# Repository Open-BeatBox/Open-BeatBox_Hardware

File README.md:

# Open-BEATBox — Hardware

CAD sources, electronics designs and production files for the Open-BEATBox
apparatus.

## Contents

- `mechanical/` — 3D models and production files (3D printing, laser cutting) for the enclosure and modules, two hardware generations, **V2** and **V3**.
- `electronics/` — KiCad circuit-board designs and manufacturing files for the V3 modules.

## `mechanical/`

### `mechanical/V2/`

SolidWorks sources (`.SLDPRT` parts, `.SLDASM` assemblies), reference renders
(`.png`) and one drawing (`cage_1feeder_2screens.pdf`), organised per module:

| Folder | Module |
| --- | --- |
| `baseCage/` | base cage |
| `cage_1feeder_2screens/` | cage assembly with one feeder and two screens |
| `camera/` | camera and NeoPixel ring support |
| `feeder/` | feeder part and assembly |
| `passage/` | passage |
| `screen/` | screen frame |

Each module has a `production/` subfolder with the files sent to manufacturing:
`.STL` meshes for 3D printing, `.DXF` outlines for laser cutting (the filenames
carry the intended material and thickness, e.g. `..._3mm_clear.DXF`), and
sliced `.gcode` whose filenames indicate a Creality K1 Max, 0.4 mm nozzle and
Hyper PLA.

### `mechanical/V3/`

Neutral-format sources per module — `feeder/`, `lighting/`, `main/` (Raspberry
Pi shield), `screen/`, `tunnel/` — each with a `.STEP` file, a `.zip` archive
of the native CAD project, and a `PRODUCTION/` subfolder of `.STL` files (plus
one `.DXF` under `lighting/`). Alongside the modules:

| Folder | Contents |
| --- | --- |
| `enclosure/` | 3 mm wall, door and ceiling panels and the 10 mm base plate as `.DXF` for laser cutting, plus the door knob `.STL` |
| `structure/` | base plate `.DXF` and pillar `.STL` |
| `final_assembly/` | `.zip` archive of the complete assembly |

## `electronics/`

One KiCad project per PCB (`BB_RPI_shield_V1`, `BB_feeder_main_V1`,
`BB_feeder_IRBarrier_V1`, `BB_lighting_V1`, `BB_screen_main_V1`,
`BB_IR_light_curtain_V2_38k`, `BB_tunnel_V1`, `BB_nosepoke_V1`), each with its
schematic exported to PDF and a `production/` folder holding the Gerber `.zip`,
BOM, pick-and-place files and IPC netlist. `STEPs/` has 3D models of the
boards and `pictures/` has renders. See
[`electronics/README.md`](./electronics/README.md) for what each board does.

Component datasheets are not included: they are the manufacturers' documents,
available from their websites (the BOM in each `production/` folder names the
parts).

## Large files

`.zip` and `.STEP` files are stored with [Git LFS](https://git-lfs.com/).
Install it before cloning (`git lfs install`), or those files will arrive as
small pointer files. Release archives and the Zenodo record contain the full
files.

## History

`mechanical/V3/` and `electronics/` were imported with their full commit history
from the ICM GitLab project `icm-institute/rnd/projects/burguiere_beatbox_website`
(`02_CAD_files/V3` and `03_ECAD_files` on its `main` branch). They were later
renamed from `CAD_files/` and `ECAD_files/`; use `git log --follow <file>` to
see a file's history across the renames.

## Licence

CERN Open Hardware Licence Version 2 — Strongly Reciprocal
(**CERN-OHL-S-2.0**). See [`LICENSE`](./LICENSE).

## Citing

If you use these designs in published work, please cite **both**:

1. the reference preprint of the platform:

   > Euvrard M, Benzina N, Domingues D, Mondragón-González SL, Huzard D, Penderia G, Travert-Jouanneau Y, Lavielle O, Lousada E, Schreiweis C, Lorenz A, Pavlov P, Ajili Z, Lebegue L, Tissier P, Burguière E. "Open-BEATBox: an open-source autonomous operant chamber for high-throughput data acquisition of complex behaviour." bioRxiv, 2026. doi: [10.64898/2026.11.07.765109](https://doi.org/10.64898/2026.11.07.765109)

2. the Zenodo record of the release you used. Each release of this repository
   is archived on Zenodo with its own DOI; the version described in the
   preprint is release `biorxiv-v1` (DOI [10.5281/zenodo.24080048](https://doi.org/10.5281/zenodo.24080048);
   all versions: [10.5281/zenodo.24080047](https://doi.org/10.5281/zenodo.24080047)). `CITATION.cff` carries the metadata (GitHub's
   *Cite this repository* button).

## Related repositories

- [Open-BeatBox_Software](https://github.com/Open-BeatBox/Open-BeatBox_Software) — PC application and module firmware (AGPL-3.0-or-later)
- [Open-BeatBox_Documentation](https://github.com/Open-BeatBox/Open-BeatBox_Documentation) — manual, assembly tutorials, Master BOM (CC-BY-4.0)
- [Open-BeatBox.github.io](https://github.com/Open-BeatBox/Open-BeatBox.github.io) — project website and manual build pipeline
- [Open-BeatBox_Firmware](https://github.com/Open-BeatBox/Open-BeatBox_Firmware) — placeholder pointing to the firmware in the Software repository

## Project links

- Project website: https://open-beatbox.github.io/
- Manual: https://open-beatbox.github.io/docs/manual/

## Issues

Please report problems with these CAD and electronics files in this repository's
[issue tracker](https://github.com/Open-BeatBox/Open-BeatBox_Hardware/issues).

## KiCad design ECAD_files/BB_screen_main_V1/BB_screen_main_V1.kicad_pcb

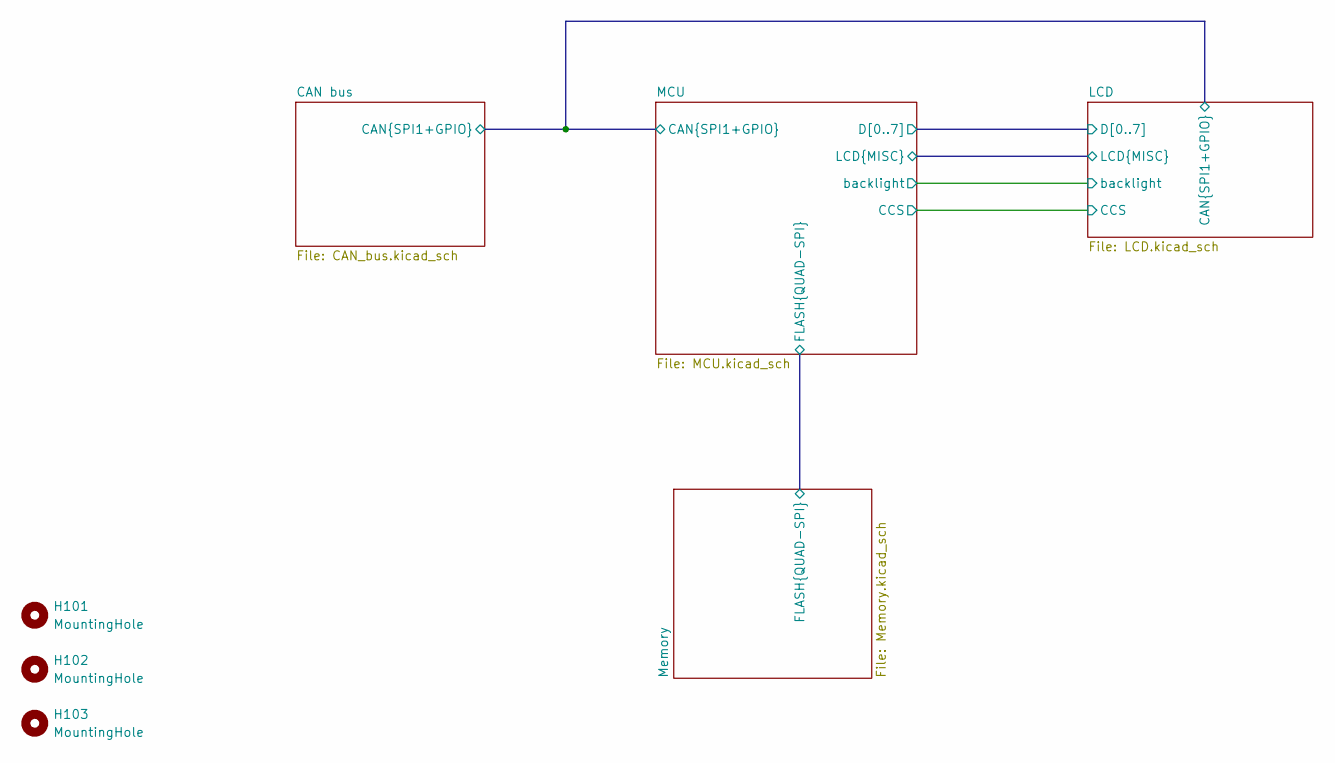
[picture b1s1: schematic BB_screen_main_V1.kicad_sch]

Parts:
H101, H102, H103: MountingHole; MountingHole_3.2mm_M3_Pad_TopBottom

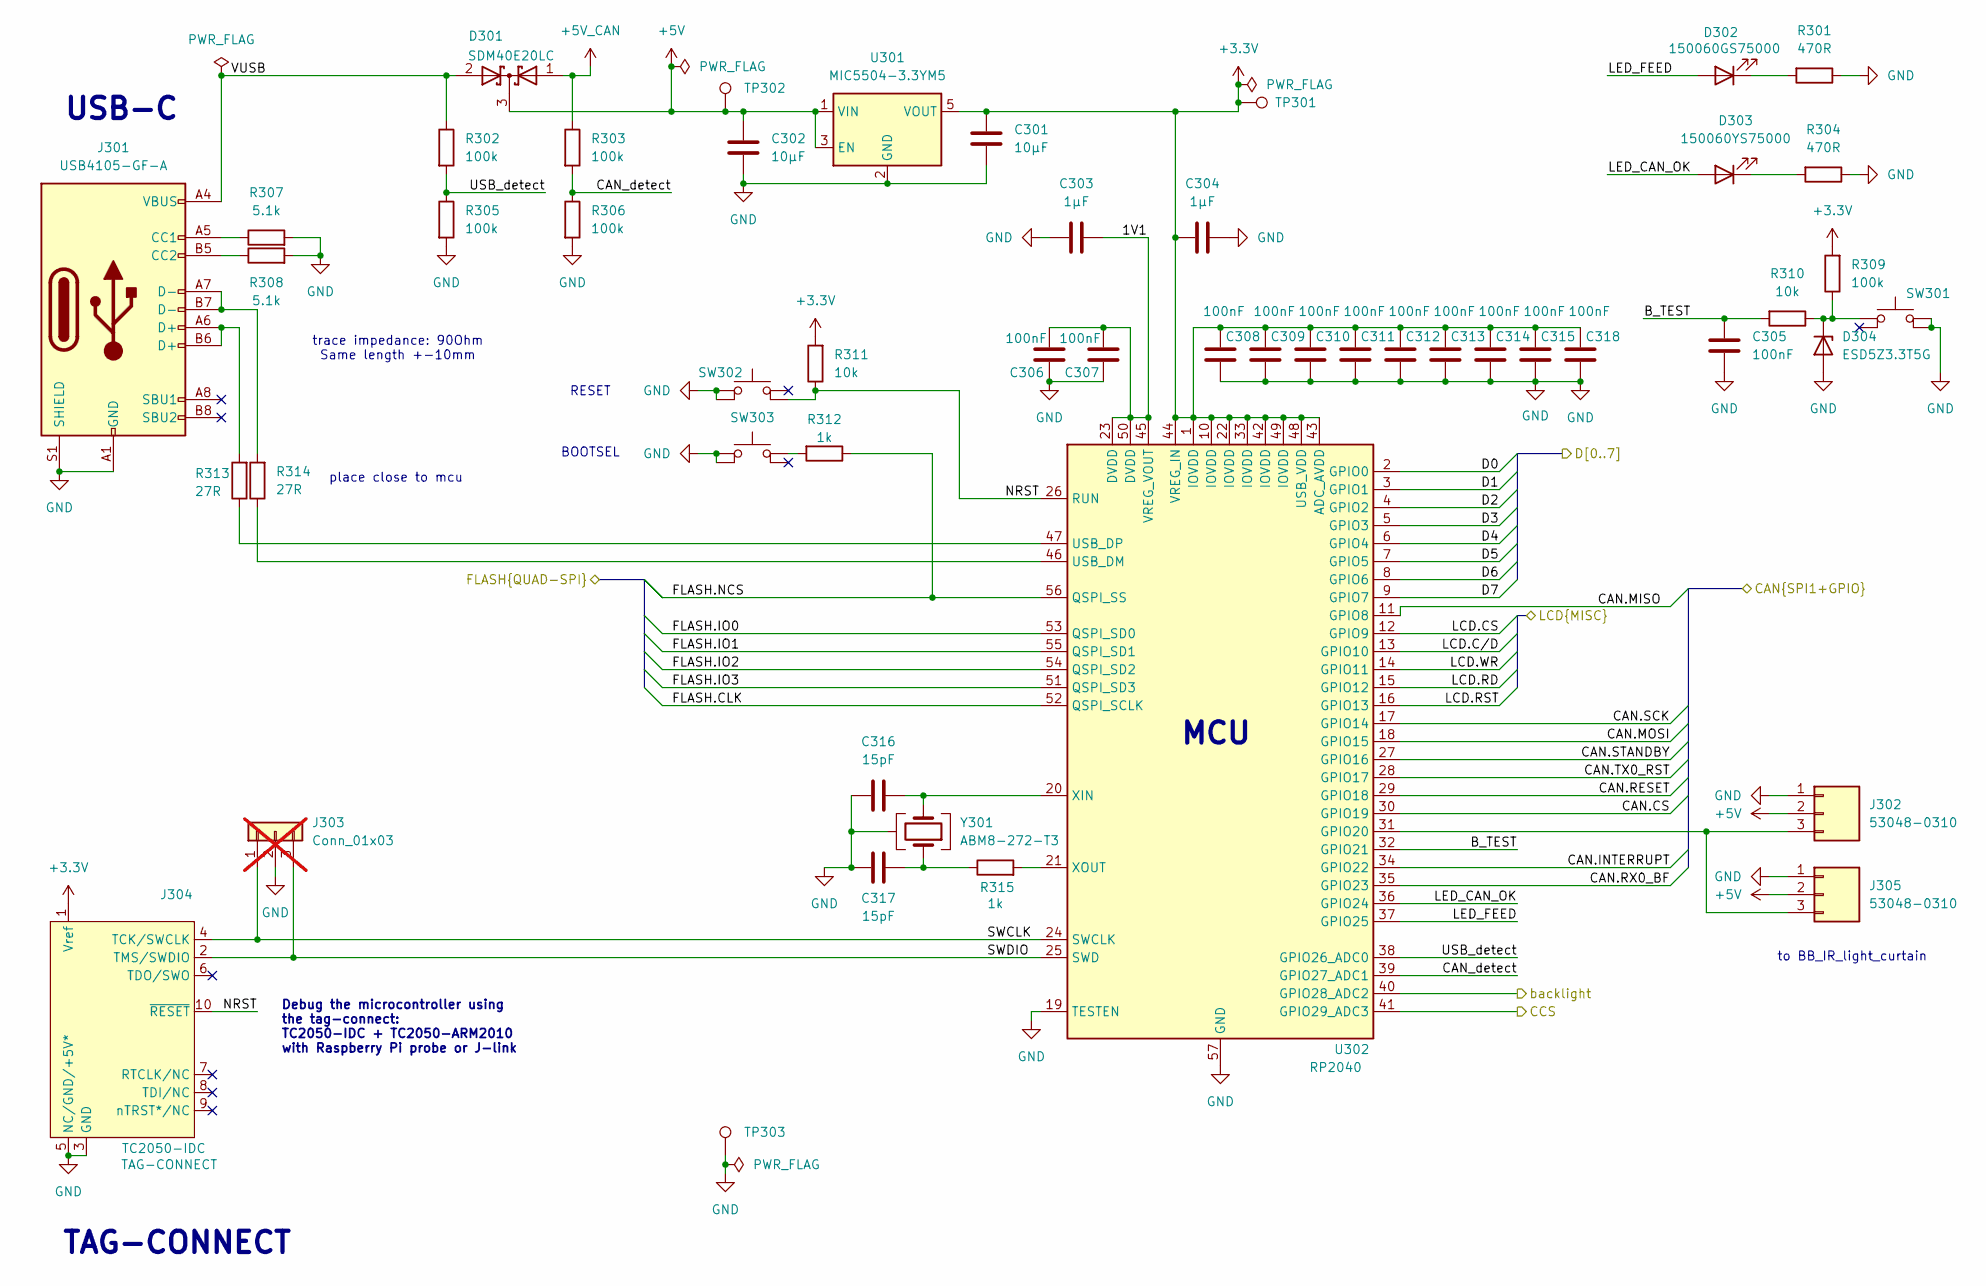
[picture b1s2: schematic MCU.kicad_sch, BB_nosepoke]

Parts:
C301, C302: 10µF; C_0603_1608Metric
C303, C304: 1µF; C_0603_1608Metric
C305, C306, C307, C308, C309, C310, C311, C312, C313, C314, C315, C318: 100nF; C_0603_1608Metric
C316, C317: 15pF; C_0603_1608Metric
D301: D_SDM40E20LC; SOT-23; MPN SDM40E20LC; JLC Part C155330
D302: LED_150060GS75000; LED_0603_1608Metric; MPN 150060GS75000; JLC Part C5252984
D303: LED_150060YS75000; LED_0603_1608Metric; MPN 150060YS75000; JLC Part C6784997
D304: TVS_ESD5Z3.3T5G; D_SOD-523; MPN ESD5Z3.3T5G; JLC Part C22440024
J301: Conn_USB-C_USB4105-GF-A; Conn_USB_C_Receptacle_GCT_USB4105-xx-A_16P_TopMnt_Horizontal; MPN USB4105-GF-A; JLC Part C393939
J302, J305: Conn_Picoblade_Molex_53048-0310; Conn_Molex_PicoBlade_53048-0310_1x03_P1.25mm_Horizontal; MPN 53048-0310; JLC Part C505275
J303: Conn_01x03; PinHeader_1x03_P2.54mm_Vertical; not fitted
J304: Conn_TagConnect_TC2050-IDC; Tag-Connect_TC2050-IDC-FP_2x05_P1.27mm_Vertical; MPN TC2050-IDC
R301, R304: 470R; R_0603_1608Metric
R302, R303, R305, R306, R309: 100k; R_0603_1608Metric
R307, R308: 5.1k; R_0603_1608Metric
R310, R311: 10k; R_0603_1608Metric
R312, R315: 1k; R_0603_1608Metric
R313, R314: 27R; R_0603_1608Metric
SW301, SW302, SW303: SW_TL3305AF160QG; SW_Push_TL3305; MPN TL3305AF160QG; JLC Part C18078070
TP301, TP302, TP303: TestPoint; TestPoint_THTPad_D2.0mm_Drill1.0mm
U301: MIC5504-3.3YM5; SOT-23-5; MPN MIC5504-3.3YM5; JLC Part C88419
U302: RP2040; QFN-56-1EP_7x7mm_P0.4mm_EP3.2x3.2mm; MPN RP2040; JLC Part C2040
Y301: Crystal_ABM8-272-T3; Crystal_SMD_Abracon_ABM8; MPN ABM8-272-T3; JLC Part C20625731

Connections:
+3.3V: C301.1, C304.1, C308.1, C309.1, C310.1, C311.1, C312.1, C313.1, C314.1, C315.1, C318.1, J304.1 (Vref), R309.2, R311.2, TP301.1 (1_1), U301.5 (VOUT), U302.1 (IOVDD), U302.10 (IOVDD), U302.22 (IOVDD), U302.33 (IOVDD), U302.42 (IOVDD), U302.43 (ADC_AVDD), U302.44 (VREG_IN), U302.48 (USB_VDD), U302.49 (IOVDD); also elsewhere on the board
/CAN bus/CAN.CS: U302.30 (GPIO19); also elsewhere on the board
/CAN bus/CAN.INTERRUPT: U302.34 (GPIO22); also elsewhere on the board
/CAN bus/CAN.MISO: U302.11 (GPIO8); also elsewhere on the board
/CAN bus/CAN.MOSI: U302.18 (GPIO15); also elsewhere on the board
/CAN bus/CAN.RESET: U302.29 (GPIO18); also elsewhere on the board
/CAN bus/CAN.RX0_BF: U302.35 (GPIO23); also elsewhere on the board
/CAN bus/CAN.SCK: U302.17 (GPIO14); also elsewhere on the board
/CAN bus/CAN.STANDBY: U302.27 (GPIO16); also elsewhere on the board
/CAN bus/CAN.TX0_RST: U302.28 (GPIO17); also elsewhere on the board
/LCD/CCS: R302.2, R305.1, U302.38 (GPIO26_ADC0); also elsewhere on the board
/LCD/D0: U302.2 (GPIO0); also elsewhere on the board
/LCD/D1: U302.3 (GPIO1); also elsewhere on the board
/LCD/D2: U302.4 (GPIO2); also elsewhere on the board
/LCD/D3: U302.5 (GPIO3); also elsewhere on the board
/LCD/D4: U302.6 (GPIO4); also elsewhere on the board
/LCD/D5: U302.7 (GPIO5); also elsewhere on the board
/LCD/D6: U302.8 (GPIO6); also elsewhere on the board
/LCD/D7: U302.9 (GPIO7); also elsewhere on the board
/LCD/LCD.CS: U302.12 (GPIO9); also elsewhere on the board
/LCD/LCD.C/D: U302.13 (GPIO10); also elsewhere on the board
/LCD/LCD.RD: U302.15 (GPIO12); also elsewhere on the board
/LCD/LCD.RST: U302.16 (GPIO13); also elsewhere on the board
/LCD/LCD.WR: U302.14 (GPIO11); also elsewhere on the board
/LCD/backlight: U302.40 (GPIO28_ADC2); also elsewhere on the board
/MCU/1V1: C303.2, C306.2, C307.1, U302.23 (DVDD), U302.45 (VREG_VOUT), U302.50 (DVDD)
/MCU/B_TEST: C305.1, R310.2, U302.32 (GPIO21)
/MCU/CAN_detect: R303.2, R306.1, U302.39 (GPIO27_ADC1)
/MCU/FLASH.CLK: U302.52 (QSPI_SCLK); also elsewhere on the board
/MCU/FLASH.IO0: U302.53 (QSPI_SD0); also elsewhere on the board
/MCU/FLASH.IO1: U302.55 (QSPI_SD1); also elsewhere on the board
/MCU/FLASH.IO2: U302.54 (QSPI_SD2); also elsewhere on the board
/MCU/FLASH.IO3: U302.51 (QSPI_SD3); also elsewhere on the board
/MCU/FLASH.NCS: R312.1, U302.56 (QSPI_SS); also elsewhere on the board
/MCU/LED_CAN_OK: D303.2 (A), U302.36 (GPIO24)
/MCU/LED_FEED: D302.2 (A), U302.37 (GPIO25)
/MCU/NRST: J304.10 (~RESET), R311.1, SW302.2, U302.26 (RUN)
/MCU/SWCLK: J303.1, J304.4 (TCK/SWCLK), U302.24 (SWCLK)
/MCU/SWDIO: J303.3, J304.2 (TMS/SWDIO), U302.25 (SWD)
/MCU/VUSB: D301.2 (A), J301.A4 (VBUS), J301.A9 (VBUS), J301.B4 (VBUS), J301.B9 (VBUS), R302.1; also elsewhere on the board
GND: C301.2, C302.2, C303.1, C304.2, C305.2, C306.1, C307.2, C308.2, C309.2, C310.2, C311.2, C312.2, C313.2, C314.2, C315.2, C316.1, C317.1, C318.2, D304.2 (A), J301.A1 (GND), J301.A12 (GND), J301.B1 (GND), J301.B12 (GND), J301.S1 (SHIELD), J302.1, J303.2, J304.3 (GND), J304.5 (NC/GND/+5V*), J305.1, R301.1, R304.1, R305.2, R306.2, R307.2, R308.2, SW301.1, SW301.2, SW302.3, SW302.4, SW303.1, SW303.2, TP303.1 (1_1), U301.2 (GND), U302.19 (TESTEN), U302.57 (GND), Y301.2, Y301.4; also elsewhere on the board
unnamed: C317.2, R315.1, Y301.1
unnamed: D302.1 (K), R301.2
unnamed: D303.1 (K), R304.2
unnamed: D304.1 (K), R309.1, R310.1, SW301.3
unnamed: J301.A5 (CC1), R307.1
unnamed: J301.B5 (CC2), R308.1
unnamed: J301.A6 (D+), J301.B6 (D+), R313.2
unnamed: J301.A7 (D-), J301.B7 (D-), R314.2
unnamed: J302.3, J305.3, U302.31 (GPIO20)
unnamed: R312.2, SW303.3
unnamed 60: U302.41 (GPIO29_ADC3); also elsewhere on the board
unnamed: R314.1, U302.46 (USB_DM)
unnamed: R313.1, U302.47 (USB_DP)
unnamed: C316.2, U302.20 (XIN), Y301.3
unnamed: R315.2, U302.21 (XOUT)

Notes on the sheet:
trace impedance: 90Ohm Same length +-10mm
TAG-CONNECT
MCU
place close to mcu
BOOTSEL
Debug the microcontroller using the tag-connect: TC2050-IDC + TC2050-ARM2010 with Raspberry Pi probe or J-link
RESET
USB-C
to BB_IR_light_curtain

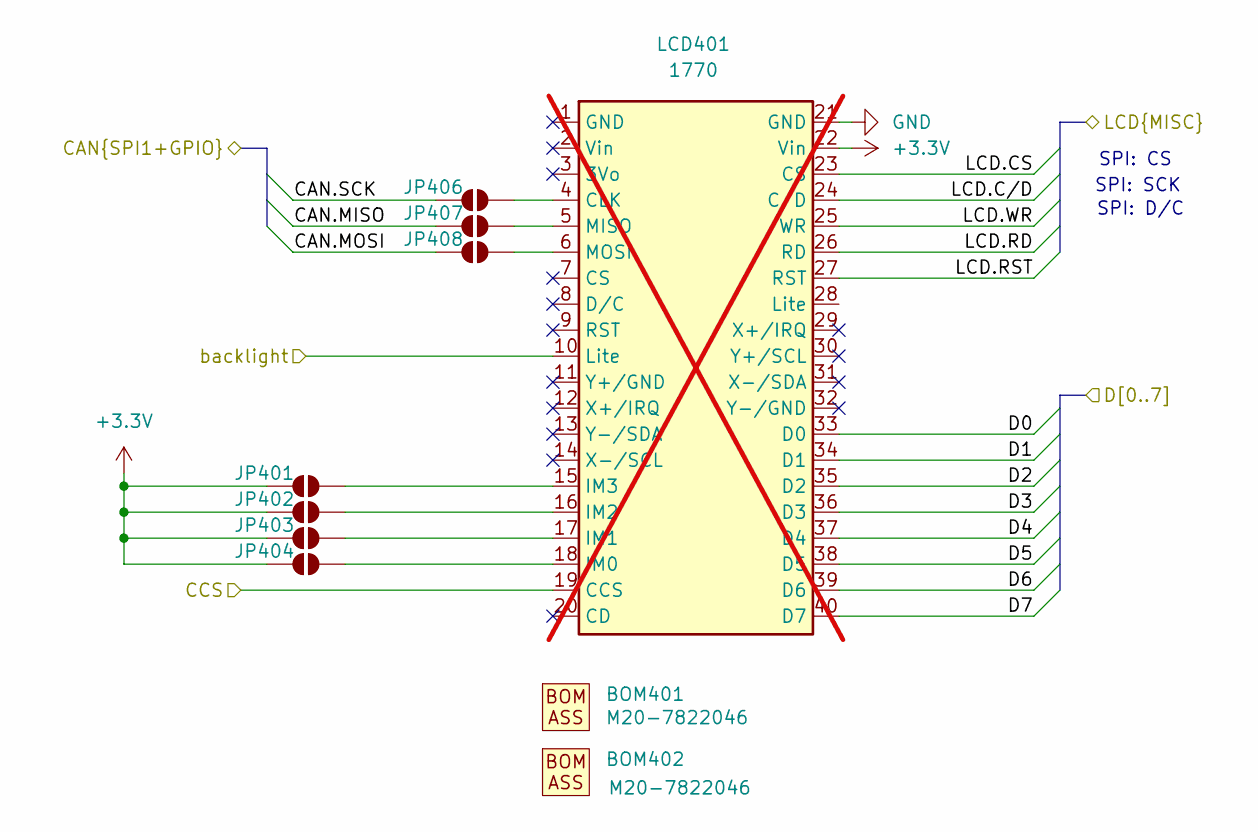
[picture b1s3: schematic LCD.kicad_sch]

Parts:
BOM401, BOM402: M20-7822046; Placeholder; MPN M20-7822046; JLC Part C7499336
JP401, JP402, JP403, JP404, JP406, JP407, JP408: SolderJumper_2_Open; SolderJumper-2_P1.3mm_Open_RoundedPad1.0x1.5mm
LCD401: 1770; Adafruit_2.8_TFT_LCD_1771; MPN 1770; not fitted

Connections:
+3.3V: JP401.1 (A), JP402.1 (A), JP403.1 (A), JP404.1 (A), LCD401.22 (Vin); also elsewhere on the board
/CAN bus/CAN.MISO: JP407.1 (A); also elsewhere on the board
/CAN bus/CAN.MOSI: JP408.1 (A); also elsewhere on the board
/CAN bus/CAN.SCK: JP406.1 (A); also elsewhere on the board
/LCD/CCS: LCD401.19 (CCS); also elsewhere on the board
/LCD/D0: LCD401.33 (D0); also elsewhere on the board
/LCD/D1: LCD401.34 (D1); also elsewhere on the board
/LCD/D2: LCD401.35 (D2); also elsewhere on the board
/LCD/D3: LCD401.36 (D3); also elsewhere on the board
/LCD/D4: LCD401.37 (D4); also elsewhere on the board
/LCD/D5: LCD401.38 (D5); also elsewhere on the board
/LCD/D6: LCD401.39 (D6); also elsewhere on the board
/LCD/D7: LCD401.40 (D7); also elsewhere on the board
/LCD/LCD.CS: LCD401.23 (CS); also elsewhere on the board
/LCD/LCD.C/D: LCD401.24 (C/D); also elsewhere on the board
/LCD/LCD.RD: LCD401.26 (RD); also elsewhere on the board
/LCD/LCD.RST: LCD401.27 (RST); also elsewhere on the board
/LCD/LCD.WR: LCD401.25 (WR); also elsewhere on the board
/LCD/backlight: LCD401.10 (Lite); also elsewhere on the board
GND: LCD401.21 (GND); also elsewhere on the board
unnamed: JP401.2 (B), LCD401.15 (IM3)
unnamed: JP402.2 (B), LCD401.16 (IM2)
unnamed: JP403.2 (B), LCD401.17 (IM1)
unnamed: JP404.2 (B), LCD401.18 (IM0)
unnamed: JP406.2 (B), LCD401.4 (CLK)
unnamed: JP407.2 (B), LCD401.5 (MISO)
unnamed: JP408.2 (B), LCD401.6 (MOSI)

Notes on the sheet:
SPI: SCK
SPI: CS
SPI: D/C

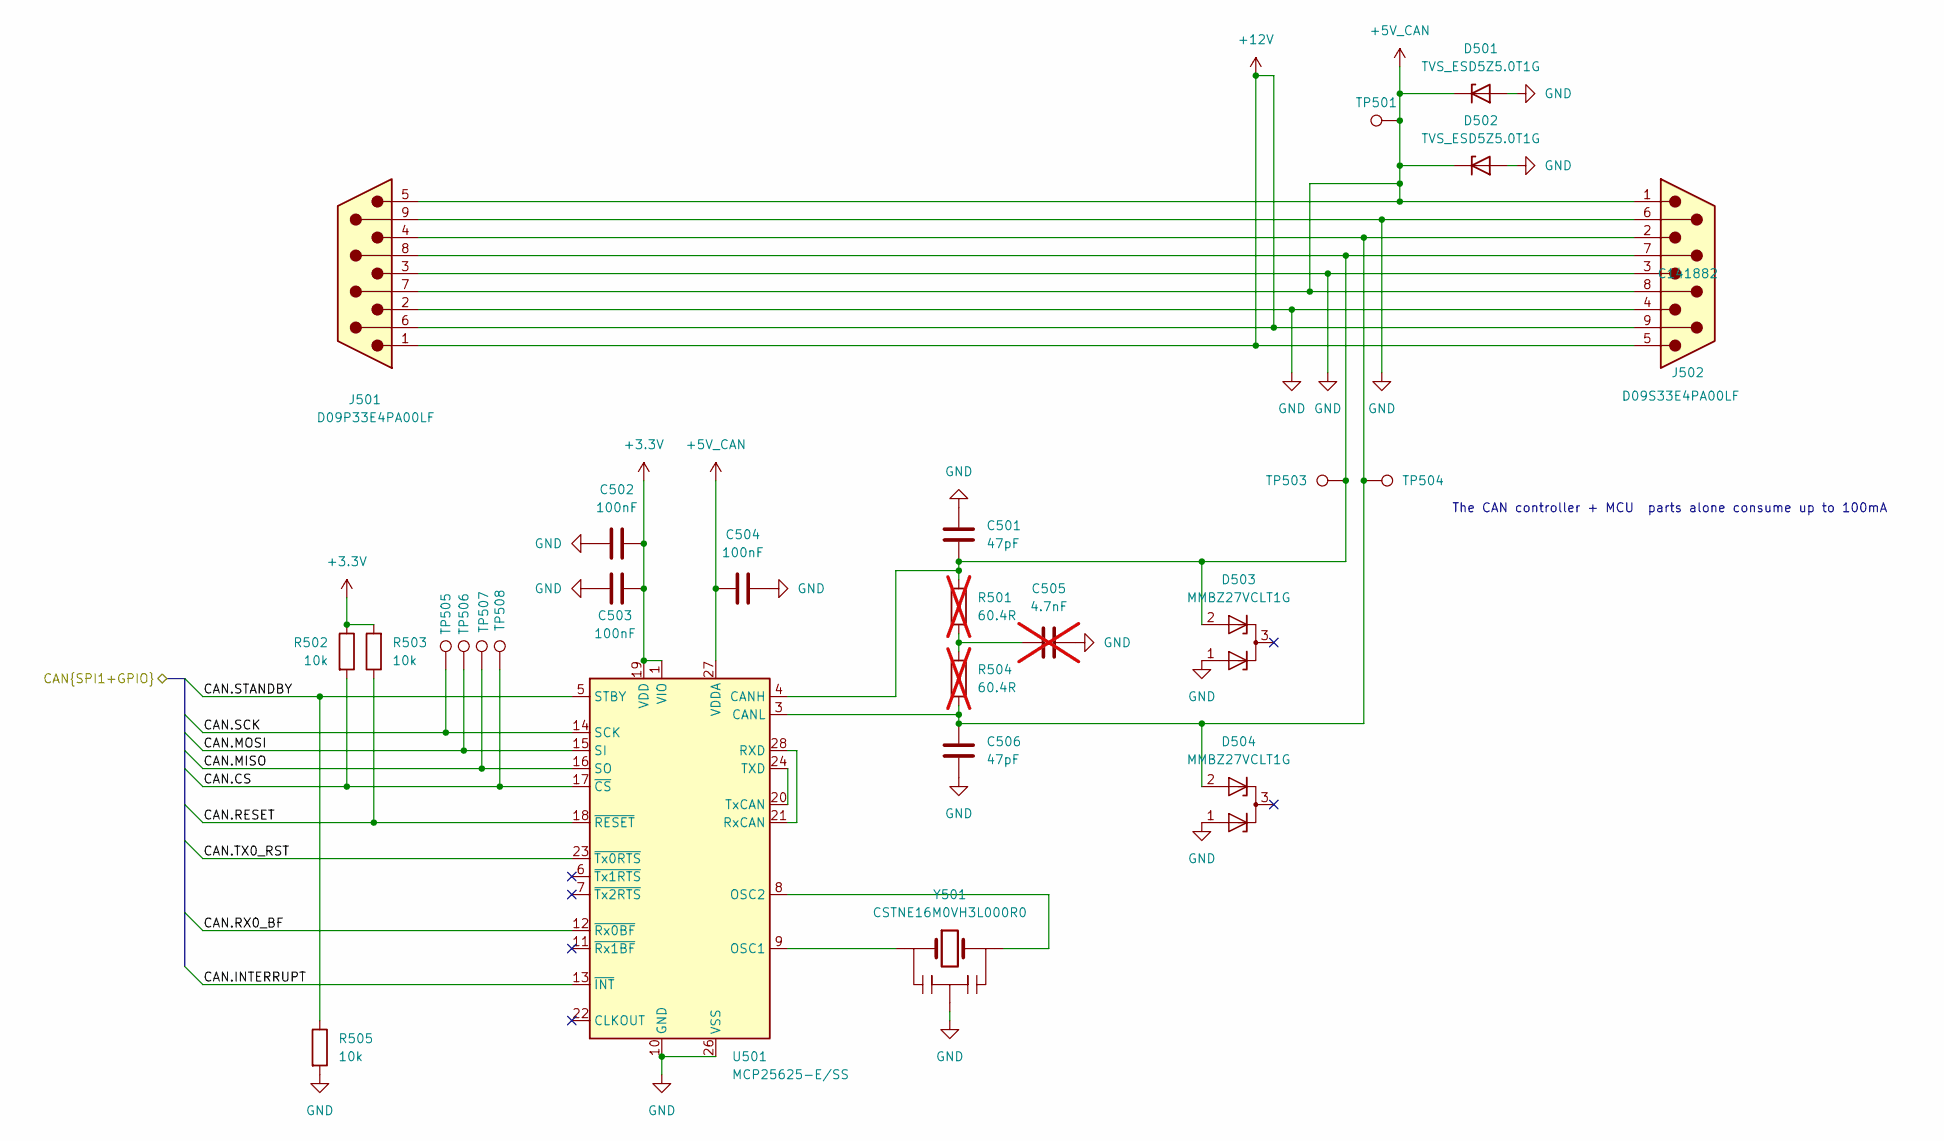
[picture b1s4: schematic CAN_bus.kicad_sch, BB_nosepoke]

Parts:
C501, C506: 47pF; C_0603_1608Metric
C502, C503, C504: 100nF; C_0603_1608Metric
C505: 4.7nF; C_0603_1608Metric; not fitted
D501, D502: TVS_ESD5Z5.0T1G; D_SOD-523; MPN ESD5Z5.0T1G; JLC Part C343989
D503, D504: MMBZ27VCLT1G; SOT-23; MPN MMBZ27VCLT1G; JLC Part C128609
J501: Conn-DB9_D09P33E4PA00LF; Conn_DB9_D09P33E4PA00LF; MPN D09P33E4PA00LF; JLC Part C19077344
J502: Conn-DB9_D09S33E4PA00LF; Conn_DB9_D09S33E4PA00LF; MPN D09S33E4PA00LF; JLC Part C141882
R501, R504: 60.4R; R_0603_1608Metric; not fitted
R502, R503, R505: 10k; R_0603_1608Metric
TP501: TestPoint; TestPoint_THTPad_D2.0mm_Drill1.0mm
TP503, TP504, TP505, TP506, TP507, TP508: TestPoint_SMD; TestPoint_Pad_D1.0mm
U501: MCP25625-E/SS; SSOP-28_5.3x10.2mm_P0.65mm; MPN MCP25625-E/SS; JLC Part C184944
Y501: CSTNE16M0VH3L000R0; Resonator_SMD_Murata_CSTxExxV-3Pin_3.0x1.1mm; MPN CSTNE16M0VH3L000R0; JLC Part C1870467

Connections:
+3.3V: C502.2, C503.2, R502.1, R503.2, U501.1 (VIO), U501.19 (VDD); also elsewhere on the board
+12V: J501.1, J501.6, J502.5, J502.9
/CAN bus/CAN.CS: R502.2, TP508.1 (1_1), U501.17 (~CS); also elsewhere on the board
/CAN bus/CAN.INTERRUPT: U501.13 (~INT); also elsewhere on the board
/CAN bus/CAN.MISO: TP507.1 (1_1), U501.16 (SO); also elsewhere on the board
/CAN bus/CAN.MOSI: TP506.1 (1_1), U501.15 (SI); also elsewhere on the board
/CAN bus/CAN.RESET: R503.1, U501.18 (~RESET); also elsewhere on the board
/CAN bus/CAN.RX0_BF: U501.12 (~Rx0BF); also elsewhere on the board
/CAN bus/CAN.SCK: TP505.1 (1_1), U501.14 (SCK); also elsewhere on the board
/CAN bus/CAN.STANDBY: R505.1, U501.5 (STBY); also elsewhere on the board
/CAN bus/CAN.TX0_RST: U501.23 (~Tx0RTS); also elsewhere on the board
GND: C501.1, C502.1, C503.1, C504.2, C505.2, C506.2, D501.2 (A), D502.2 (A), D503.1 (K), D504.1 (K), J501.2, J501.3, J501.9, J502.3, J502.4, J502.6, R505.2, U501.10 (GND), U501.26 (VSS), Y501.2 (GND); also elsewhere on the board
unnamed: C505.1, R501.1, R504.2
unnamed: C501.2, D503.2 (K), J501.8, J502.7, R501.2, TP503.1 (1_1), U501.4 (CANH)
unnamed: C506.1, D504.2 (K), J501.4, J502.2, R504.1, TP504.1 (1_1), U501.3 (CANL)
unnamed: U501.9 (OSC1), Y501.1 (Input)
unnamed: U501.8 (OSC2), Y501.3 (Output)
unnamed: U501.21 (RxCAN), U501.28 (RXD)
unnamed: U501.20 (TxCAN), U501.24 (TXD)

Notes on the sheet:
The CAN controller + MCU parts alone consume up to 100mA

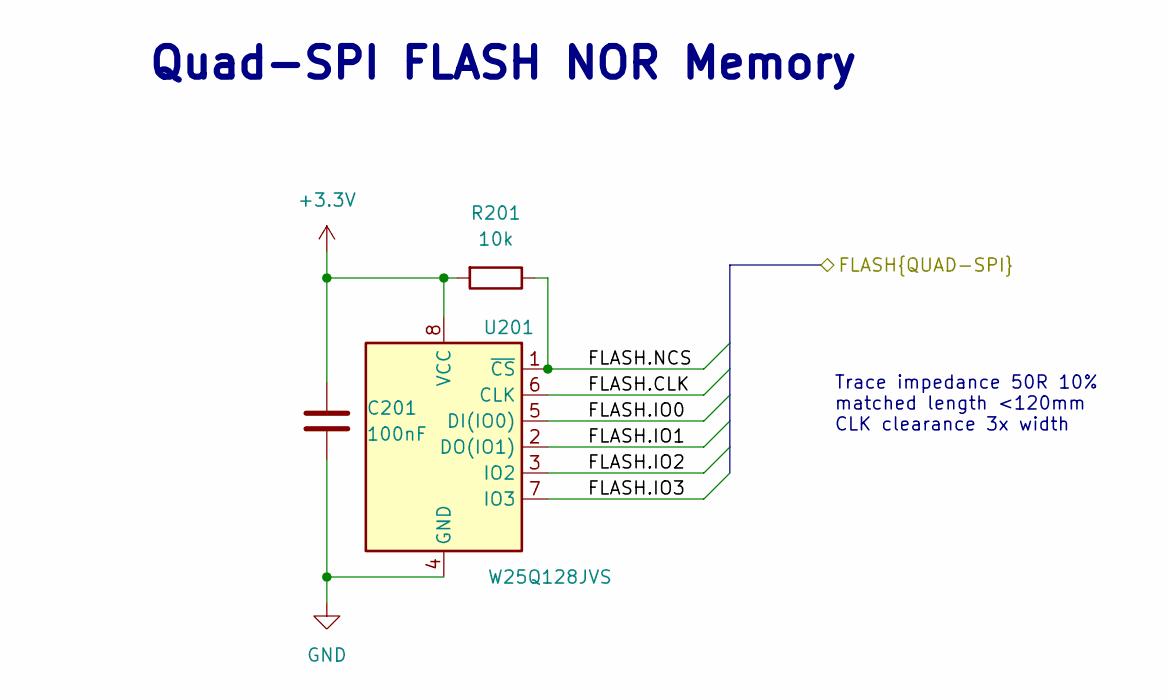
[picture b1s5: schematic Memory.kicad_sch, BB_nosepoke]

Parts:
C201: 100nF; C_0603_1608Metric
R201: 10k; R_0603_1608Metric
U201: W25Q128JVS; SOIC-8_W25Q128JV; MPN W25Q128JVS; JLC Part C97521

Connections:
+3.3V: C201.2, R201.2, U201.8 (VCC); also elsewhere on the board
/MCU/FLASH.CLK: U201.6 (CLK); also elsewhere on the board
/MCU/FLASH.IO0: U201.5 (DI(IO0)); also elsewhere on the board
/MCU/FLASH.IO1: U201.2 (DO(IO1)); also elsewhere on the board
/MCU/FLASH.IO2: U201.3 (IO2); also elsewhere on the board
/MCU/FLASH.IO3: U201.7 (IO3); also elsewhere on the board
/MCU/FLASH.NCS: R201.1, U201.1 (~CS); also elsewhere on the board
GND: C201.1, U201.4 (GND); also elsewhere on the board

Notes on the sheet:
Trace impedance 50R 10% matched length <120mm CLK clearance 3x width
Quad-SPI FLASH NOR Memory

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
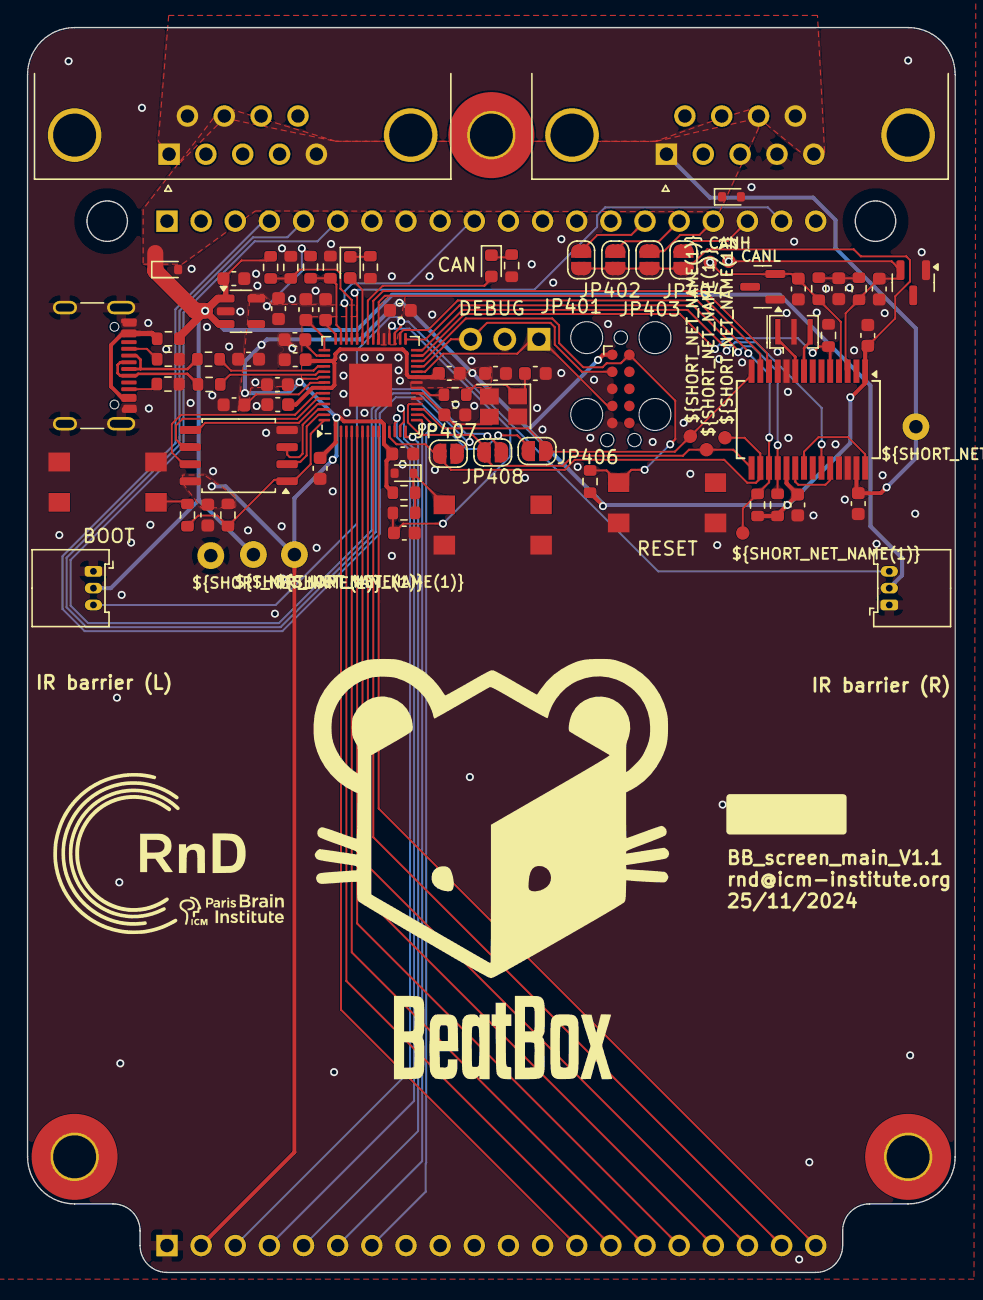
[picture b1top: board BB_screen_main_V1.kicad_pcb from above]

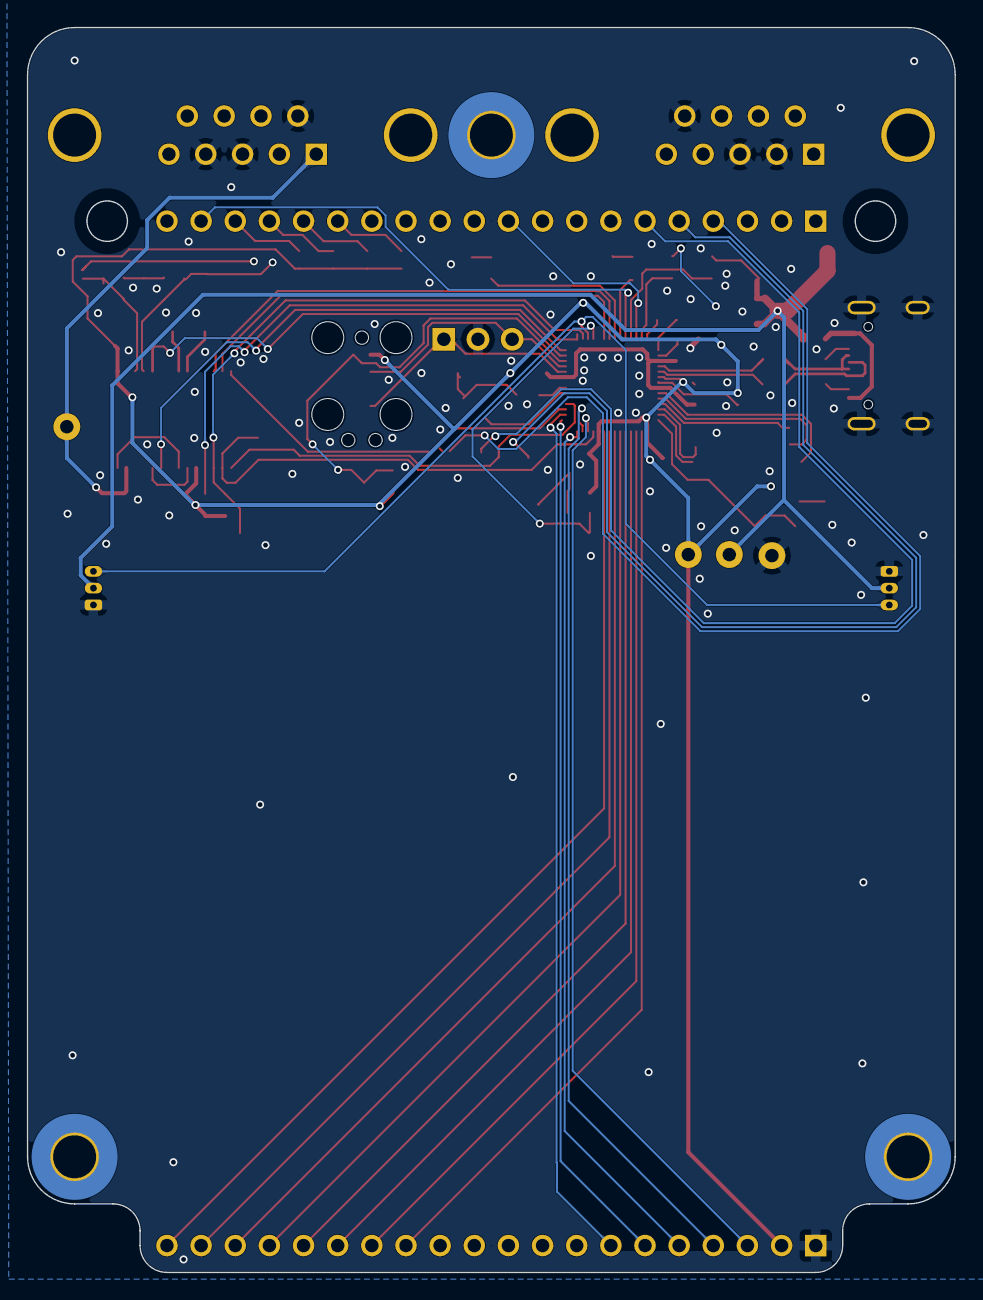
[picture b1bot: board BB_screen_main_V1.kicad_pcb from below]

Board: 4 copper layers, 69.0 x 92.6 mm, 93 parts (3 on the bottom side), 72 nets.

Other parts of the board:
R209: 100k; R_0603_1608Metric
R210: 10k; R_0603_1608Metric
R316: 0; R_0603_1608Metric

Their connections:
+3.3V: R209.1; also elsewhere on the board
/MCU/VUSB: R316.1; also elsewhere on the board
GND: R210.2; also elsewhere on the board
unnamed 60: R209.2, R210.1; also elsewhere on the board

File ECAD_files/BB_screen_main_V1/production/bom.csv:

Designator,Footprint,Quantity,Value,LCSC Part #
"BOM401, BOM402",Placeholder,2,M20-7822046,M20-7822046
"C201, C305, C306, C307, C308, C309, C310, C311, C312, C313, C314, C315, C318, C502, C503, C504",0603,16,100nF,
"C301, C302",0603,2,10µF,
"C303, C304",0603,2,1µF,
"C316, C317",0603,2,15pF,
"C501, C506",0603,2,47pF,
D302,0603,1,LED_150060GS75000,150060GS75000
D303,0603,1,LED_150060YS75000,150060YS75000
D304,D_SOD-523,1,TVS_ESD5Z3.3T5G,ESD5Z3.3T5G
"D501, D502",D_SOD-523,2,TVS_ESD5Z5.0T1G,ESD5Z5.0T1G
"D503, D504",SOT-23,2,MMBZ27VCLT1G,MMBZ27VCLT1G
J301,Conn_USB_C_Receptacle_GCT_USB4105-xx-A_16P_TopMnt_Horizontal,1,Conn_USB-C_USB4105-GF-A,USB4105-GF-A
"J302, J305",Conn_Molex_PicoBlade_53048-0310_1x03_P1.25mm_Horizontal,2,Conn_Picoblade_Molex_53048-0310,53048-0310
J501,Conn_DB9_D09P33E4PA00LF,1,Conn-DB9_D09P33E4PA00LF,D09P33E4PA00LF
J502,Conn_DB9_D09S33E4PA00LF,1,Conn-DB9_D09S33E4PA00LF,D09S33E4PA00LF
"R201, R210, R310, R311, R502, R503, R505",0603,7,10k,
"R209, R303, R306, R309",0603,4,100k,
"R301, R304",0603,2,470R,
"R307, R308",0603,2,5.1k,
"R312, R315",0603,2,1k,
"R313, R314",0603,2,27R,
"SW301, SW302, SW303",SW_Push_TL3305,3,SW_TL3305AF160QG,TL3305AF160QG
U201,SOIC-8_W25Q128JV,1,W25Q128JVS,W25Q128JVS
U301,SOT-23-5,1,MIC5504-3.3YM5,MIC5504-3.3YM5
U302,QFN-56-1EP_7x7mm_P0.4mm_EP3.2x3.2mm,1,RP2040,RP2040
U501,SSOP-28_5.3x10.2mm_P0.65mm,1,MCP25625-E/SS,MCP25625-E/SS
Y301,Crystal_SMD_Abracon_ABM8,1,Crystal_ABM8-272-T3,ABM8-272-T3
Y501,Resonator_SMD_Murata_CSTxExxV-3Pin_3.0x1.1mm,1,CSTNE16M0VH3L000R0,CSTNE16M0VH3L000R0

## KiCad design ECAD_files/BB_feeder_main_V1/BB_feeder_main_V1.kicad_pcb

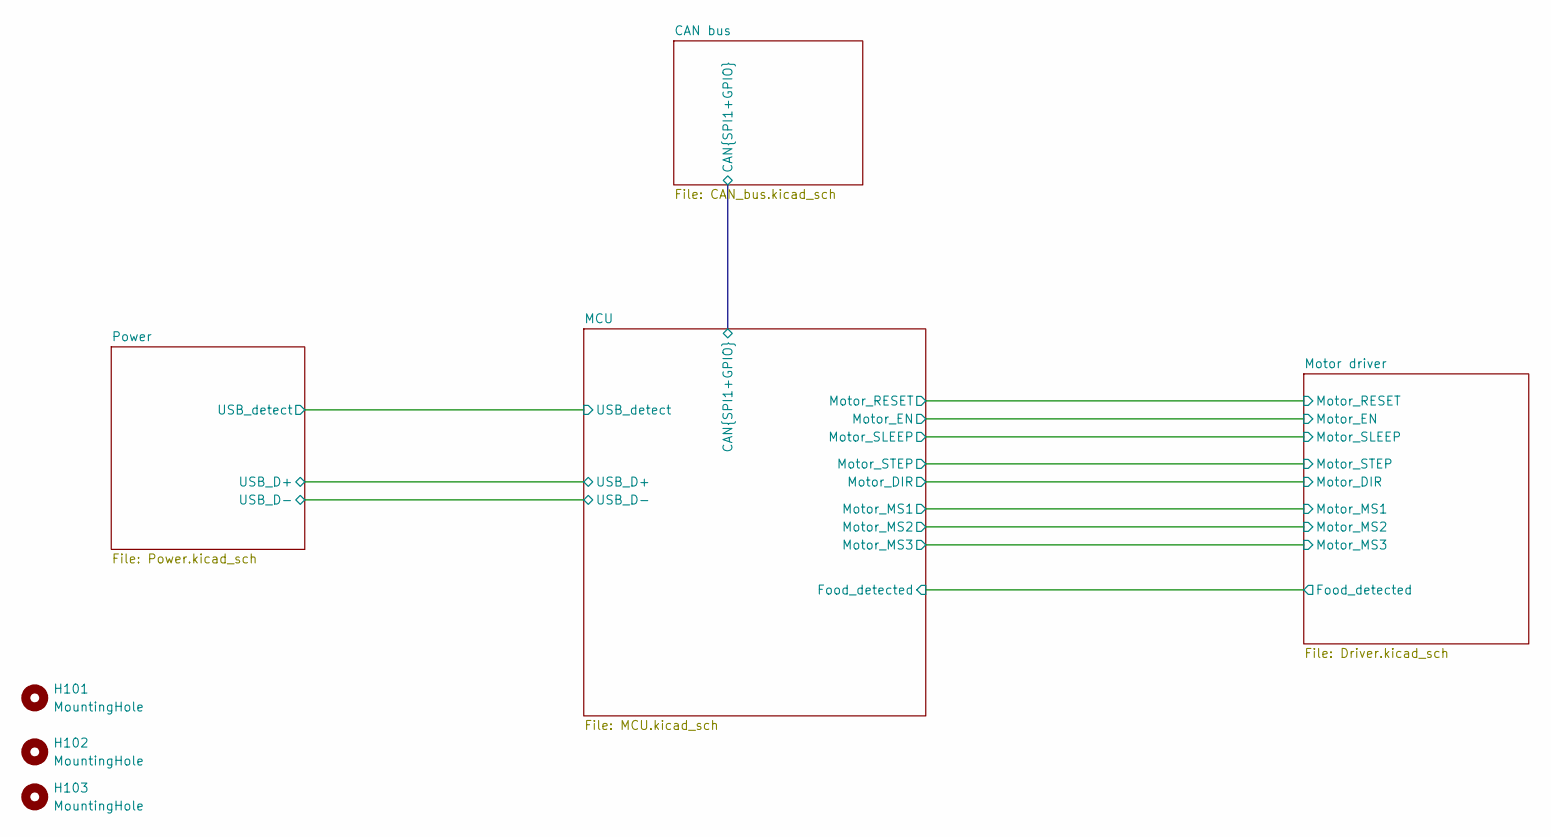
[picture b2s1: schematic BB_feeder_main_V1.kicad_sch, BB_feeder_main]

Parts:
H101, H102, H103: MountingHole; MountingHole_3.2mm_M3_Pad_TopBottom
